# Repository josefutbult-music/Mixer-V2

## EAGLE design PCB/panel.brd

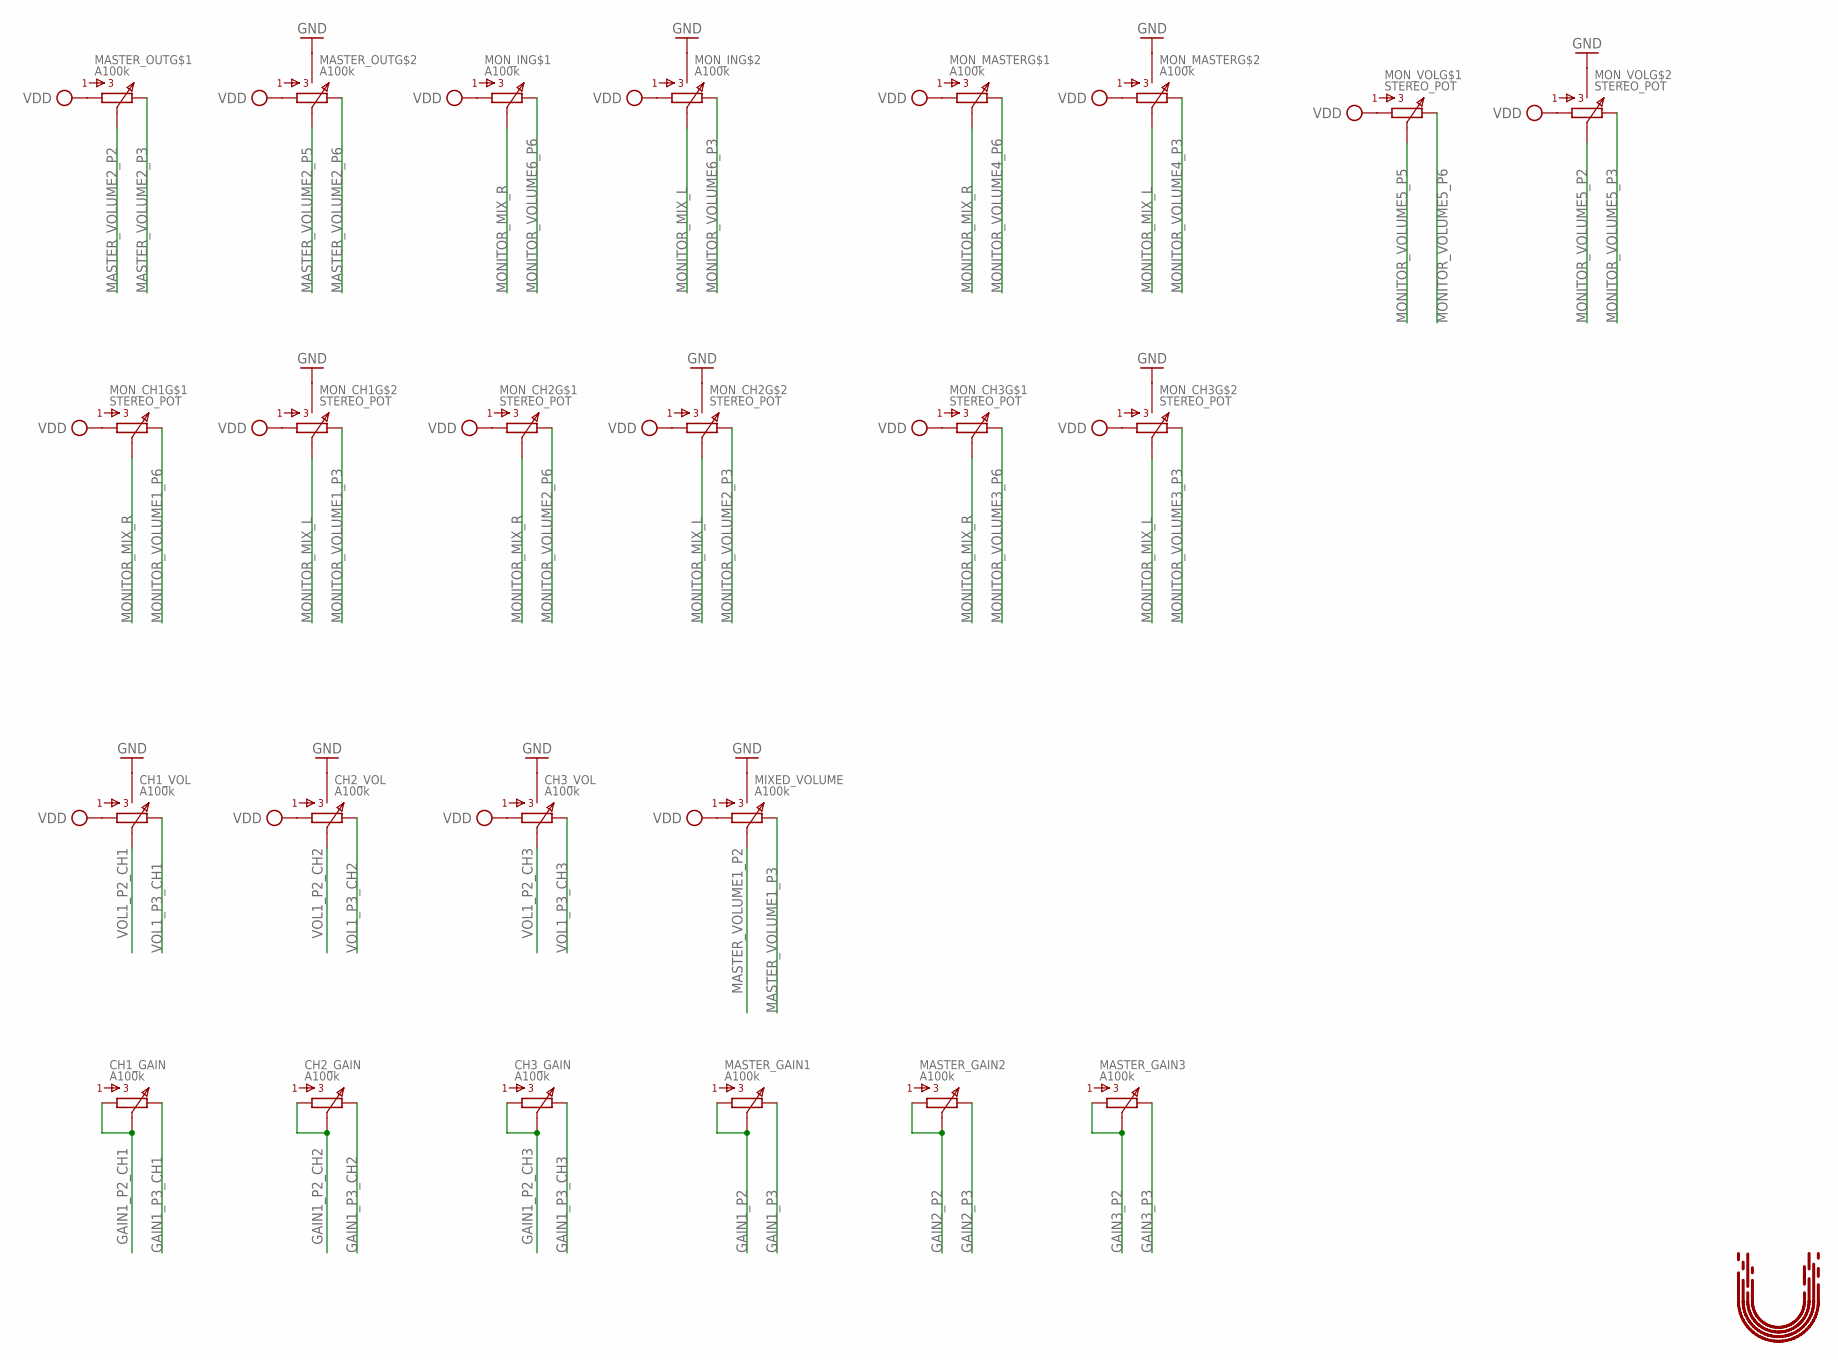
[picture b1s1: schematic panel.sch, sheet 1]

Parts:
CH1_GAIN, CH2_GAIN, CH3_GAIN: A100k; 3296W
CH1_VOL, CH2_VOL, CH3_VOL: A100k; P0915N
MASTER_GAIN1, MASTER_GAIN2, MASTER_GAIN3: A100k; 3296W
MASTER_OUT: A100k; P0925N
MIXED_VOLUME: A100k; P0915N
MON_CH1, MON_CH2, MON_CH3: STEREO_POT; P0925N
MON_IN: A100k; P0925N
MON_MASTER: A100k; P0925N
MON_VOL: STEREO_POT; P0925N
U$1: UTBULT_DESIGN4; UD_4

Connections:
GAIN1_P2: MASTER_GAIN1.P$1 (1), MASTER_GAIN1.P$2 (2); also elsewhere on the board
GAIN1_P2_CH1: CH1_GAIN.P$1 (1), CH1_GAIN.P$2 (2); also elsewhere on the board
GAIN1_P2_CH2: CH2_GAIN.P$1 (1), CH2_GAIN.P$2 (2); also elsewhere on the board
GAIN1_P2_CH3: CH3_GAIN.P$1 (1), CH3_GAIN.P$2 (2); also elsewhere on the board
GAIN1_P3: MASTER_GAIN1.P$3 (3); also elsewhere on the board
GAIN1_P3_CH1: CH1_GAIN.P$3 (3); also elsewhere on the board
GAIN1_P3_CH2: CH2_GAIN.P$3 (3); also elsewhere on the board
GAIN1_P3_CH3: CH3_GAIN.P$3 (3); also elsewhere on the board
GAIN2_P2: MASTER_GAIN2.P$1 (1), MASTER_GAIN2.P$2 (2); also elsewhere on the board
GAIN2_P3: MASTER_GAIN2.P$3 (3); also elsewhere on the board
GAIN3_P2: MASTER_GAIN3.P$1 (1), MASTER_GAIN3.P$2 (2); also elsewhere on the board
GAIN3_P3: MASTER_GAIN3.P$3 (3); also elsewhere on the board
GND: CH1_VOL.P$7, CH1_VOL.P$8, CH2_VOL.P$7, CH2_VOL.P$8, CH3_VOL.P$7, CH3_VOL.P$8, MASTER_OUT.P$7, MASTER_OUT.P$8, MIXED_VOLUME.P$7, MIXED_VOLUME.P$8, MON_CH1.P$7, MON_CH1.P$8, MON_CH2.P$7, MON_CH2.P$8, MON_CH3.P$7, MON_CH3.P$8, MON_IN.P$7, MON_IN.P$8, MON_MASTER.P$7, MON_MASTER.P$8, MON_VOL.P$7, MON_VOL.P$8; also elsewhere on the board
MASTER_VOLUME1_P2: MIXED_VOLUME.P$2 (2); also elsewhere on the board
MASTER_VOLUME1_P3: MIXED_VOLUME.P$3 (3); also elsewhere on the board
MASTER_VOLUME2_P2: MASTER_OUT.P$2 (2); also elsewhere on the board
MASTER_VOLUME2_P3: MASTER_OUT.P$3 (3); also elsewhere on the board
MASTER_VOLUME2_P5: MASTER_OUT.P$5 (2); also elsewhere on the board
MASTER_VOLUME2_P6: MASTER_OUT.P$6 (3); also elsewhere on the board
MONITOR_MIX_L: MON_CH1.P$5 (2), MON_CH2.P$5 (2), MON_CH3.P$5 (2), MON_IN.P$5 (2), MON_MASTER.P$5 (2); also elsewhere on the board
MONITOR_MIX_R: MON_CH1.P$2 (2), MON_CH2.P$2 (2), MON_CH3.P$2 (2), MON_IN.P$2 (2), MON_MASTER.P$2 (2); also elsewhere on the board
MONITOR_VOLUME1_P3: MON_CH1.P$6 (3); also elsewhere on the board
MONITOR_VOLUME1_P6: MON_CH1.P$3 (3); also elsewhere on the board
MONITOR_VOLUME2_P3: MON_CH2.P$6 (3); also elsewhere on the board
MONITOR_VOLUME2_P6: MON_CH2.P$3 (3); also elsewhere on the board
MONITOR_VOLUME3_P3: MON_CH3.P$6 (3); also elsewhere on the board
MONITOR_VOLUME3_P6: MON_CH3.P$3 (3); also elsewhere on the board
MONITOR_VOLUME4_P3: MON_MASTER.P$6 (3); also elsewhere on the board
MONITOR_VOLUME4_P6: MON_MASTER.P$3 (3); also elsewhere on the board
MONITOR_VOLUME5_P2: MON_VOL.P$5 (2); also elsewhere on the board
MONITOR_VOLUME5_P3: MON_VOL.P$6 (3); also elsewhere on the board
MONITOR_VOLUME5_P5: MON_VOL.P$2 (2); also elsewhere on the board
MONITOR_VOLUME5_P6: MON_VOL.P$3 (3); also elsewhere on the board
MONITOR_VOLUME6_P3: MON_IN.P$6 (3); also elsewhere on the board
MONITOR_VOLUME6_P6: MON_IN.P$3 (3); also elsewhere on the board
VDD: CH1_VOL.P$1 (1), CH2_VOL.P$1 (1), CH3_VOL.P$1 (1), MASTER_OUT.P$1 (1), MASTER_OUT.P$4 (1), MIXED_VOLUME.P$1 (1), MON_CH1.P$1 (1), MON_CH1.P$4 (1), MON_CH2.P$1 (1), MON_CH2.P$4 (1), MON_CH3.P$1 (1), MON_CH3.P$4 (1), MON_IN.P$1 (1), MON_IN.P$4 (1), MON_MASTER.P$1 (1), MON_MASTER.P$4 (1), MON_VOL.P$1 (1), MON_VOL.P$4 (1); also elsewhere on the board
VOL1_P2_CH1: CH1_VOL.P$2 (2); also elsewhere on the board
VOL1_P2_CH2: CH2_VOL.P$2 (2); also elsewhere on the board
VOL1_P2_CH3: CH3_VOL.P$2 (2); also elsewhere on the board
VOL1_P3_CH1: CH1_VOL.P$3 (3); also elsewhere on the board
VOL1_P3_CH2: CH2_VOL.P$3 (3); also elsewhere on the board
VOL1_P3_CH3: CH3_VOL.P$3 (3); also elsewhere on the board

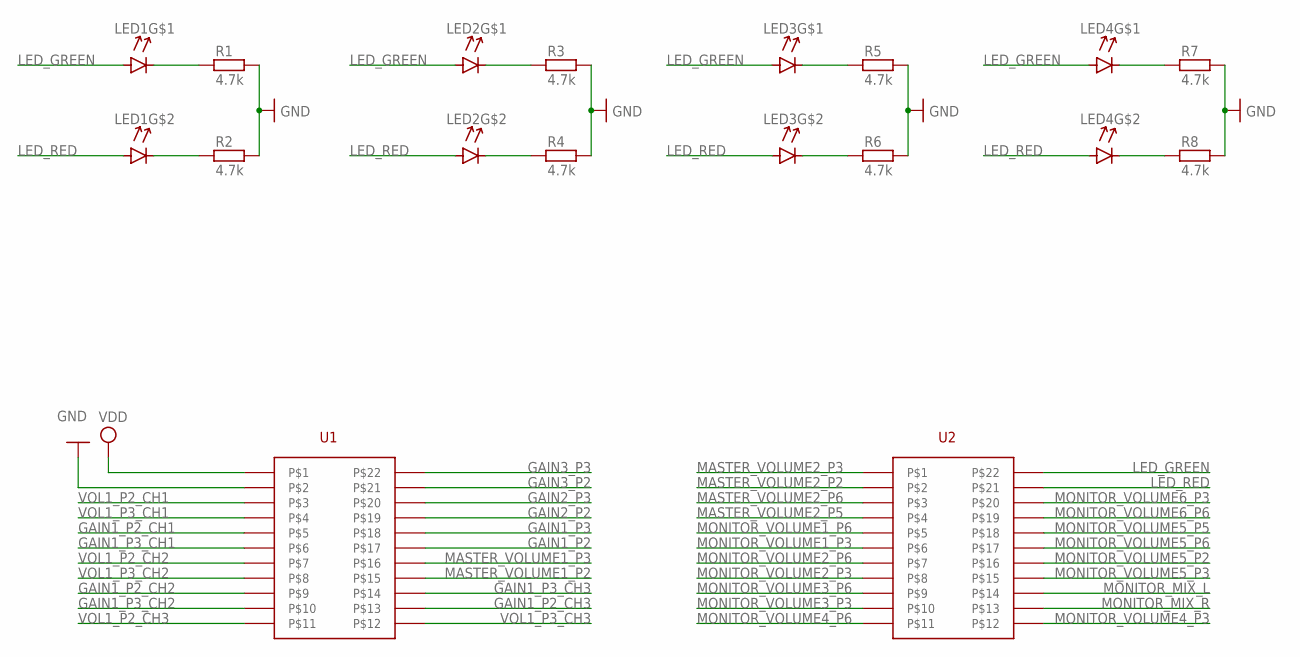
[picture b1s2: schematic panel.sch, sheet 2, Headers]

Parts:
LED1, LED2, LED3, LED4: DUAL_LEDDUAL_LED; RESCAXE40P80X160X50-4N
R1, R2, R3, R4, R5, R6, R7, R8: 4.7k; R0603
U1, U2: 22PINHEADER22PINHEADER; HDRV22W64P254_2X11_2794X508X838B

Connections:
GAIN1_P2: U1.17; also elsewhere on the board
GAIN1_P2_CH1: U1.5; also elsewhere on the board
GAIN1_P2_CH2: U1.9; also elsewhere on the board
GAIN1_P2_CH3: U1.13; also elsewhere on the board
GAIN1_P3: U1.18; also elsewhere on the board
GAIN1_P3_CH1: U1.6; also elsewhere on the board
GAIN1_P3_CH2: U1.10; also elsewhere on the board
GAIN1_P3_CH3: U1.14; also elsewhere on the board
GAIN2_P2: U1.19; also elsewhere on the board
GAIN2_P3: U1.20; also elsewhere on the board
GAIN3_P2: U1.21; also elsewhere on the board
GAIN3_P3: U1.22; also elsewhere on the board
GND: R1.2, R2.2, R3.2, R4.2, R5.2, R6.2, R7.2, R8.2, U1.2; also elsewhere on the board
LED_GREEN: LED1.1 (A), LED2.1 (A), LED3.1 (A), LED4.1 (A), U2.22
LED_RED: LED1.2 (A), LED2.2 (A), LED3.2 (A), LED4.2 (A), U2.21
MASTER_VOLUME1_P2: U1.15; also elsewhere on the board
MASTER_VOLUME1_P3: U1.16; also elsewhere on the board
MASTER_VOLUME2_P2: U2.2; also elsewhere on the board
MASTER_VOLUME2_P3: U2.1; also elsewhere on the board
MASTER_VOLUME2_P5: U2.4; also elsewhere on the board
MASTER_VOLUME2_P6: U2.3; also elsewhere on the board
MONITOR_MIX_L: U2.14; also elsewhere on the board
MONITOR_MIX_R: U2.13; also elsewhere on the board
MONITOR_VOLUME1_P3: U2.6; also elsewhere on the board
MONITOR_VOLUME1_P6: U2.5; also elsewhere on the board
MONITOR_VOLUME2_P3: U2.8; also elsewhere on the board
MONITOR_VOLUME2_P6: U2.7; also elsewhere on the board
MONITOR_VOLUME3_P3: U2.10; also elsewhere on the board
MONITOR_VOLUME3_P6: U2.9; also elsewhere on the board
MONITOR_VOLUME4_P3: U2.12; also elsewhere on the board
MONITOR_VOLUME4_P6: U2.11; also elsewhere on the board
MONITOR_VOLUME5_P2: U2.16; also elsewhere on the board
MONITOR_VOLUME5_P3: U2.15; also elsewhere on the board
MONITOR_VOLUME5_P5: U2.18; also elsewhere on the board
MONITOR_VOLUME5_P6: U2.17; also elsewhere on the board
MONITOR_VOLUME6_P3: U2.20; also elsewhere on the board
MONITOR_VOLUME6_P6: U2.19; also elsewhere on the board
unnamed: LED1.4 (C), R1.1
unnamed: LED1.3 (C), R2.1
unnamed: LED2.4 (C), R3.1
unnamed: LED2.3 (C), R4.1
unnamed: LED3.4 (C), R5.1
unnamed: LED3.3 (C), R6.1
unnamed: LED4.4 (C), R7.1
unnamed: LED4.3 (C), R8.1
VDD: U1.1; also elsewhere on the board
VOL1_P2_CH1: U1.3; also elsewhere on the board
VOL1_P2_CH2: U1.7; also elsewhere on the board
VOL1_P2_CH3: U1.11; also elsewhere on the board
VOL1_P3_CH1: U1.4; also elsewhere on the board
VOL1_P3_CH2: U1.8; also elsewhere on the board
VOL1_P3_CH3: U1.12; also elsewhere on the board

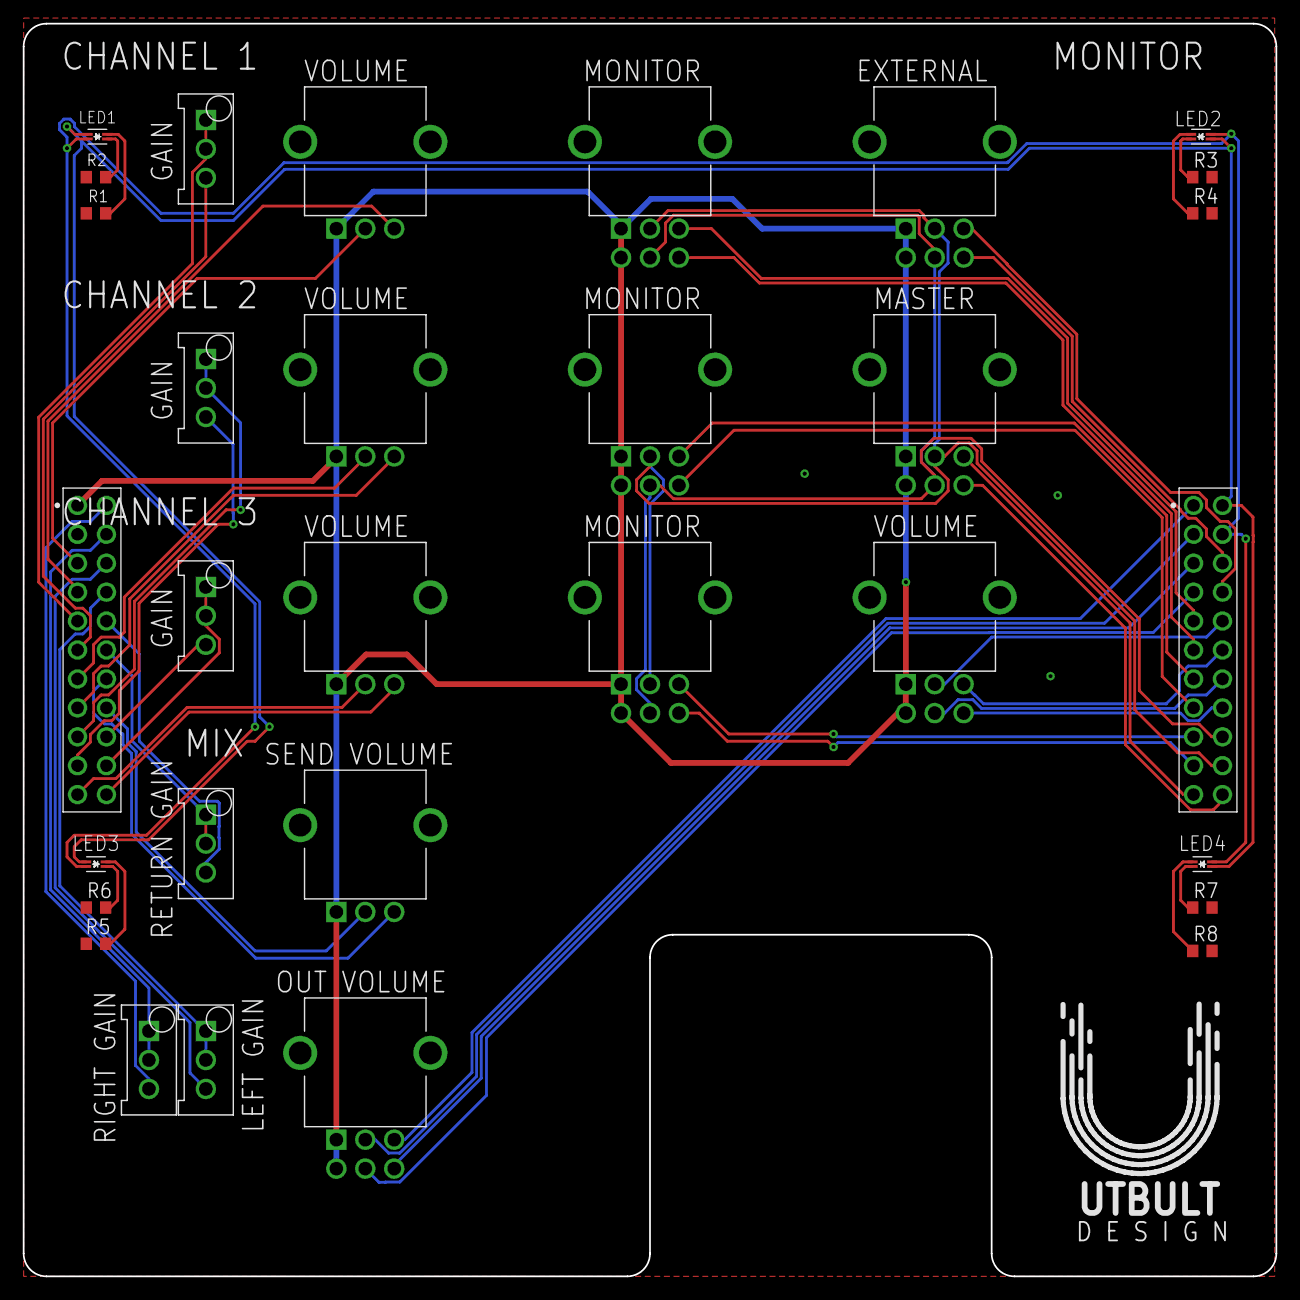
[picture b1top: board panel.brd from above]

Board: 2 copper layers, 110.0 x 110.0 mm, 32 parts (0 on the bottom side), 52 nets.

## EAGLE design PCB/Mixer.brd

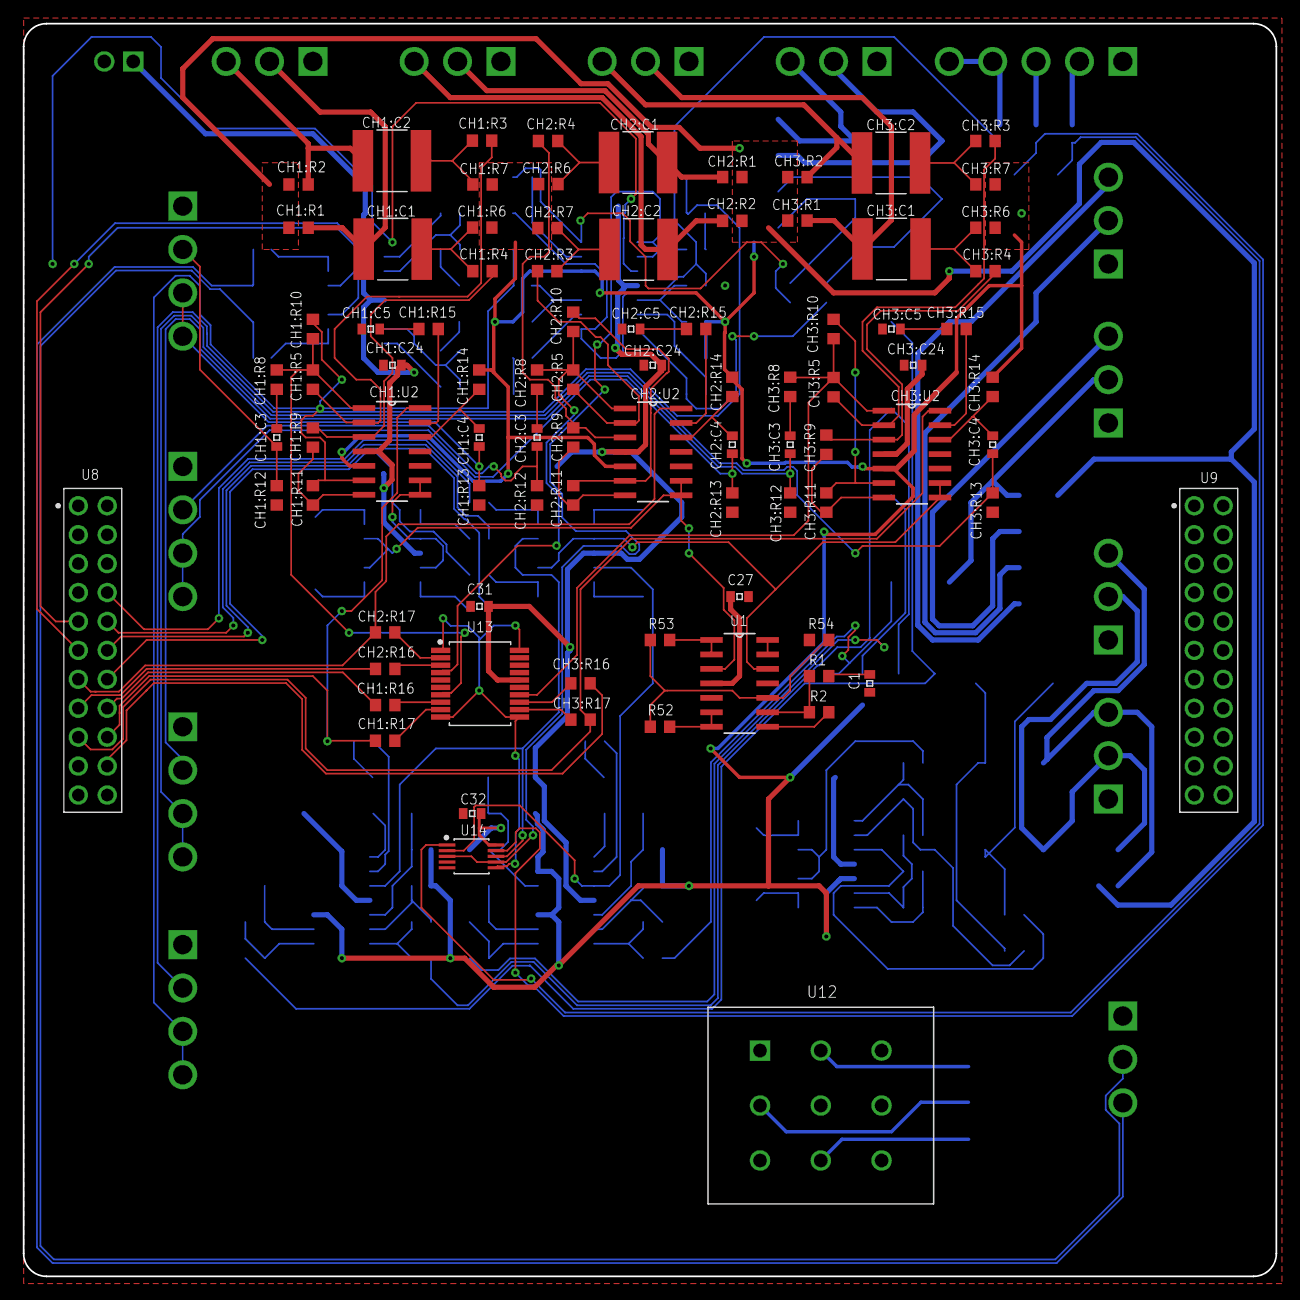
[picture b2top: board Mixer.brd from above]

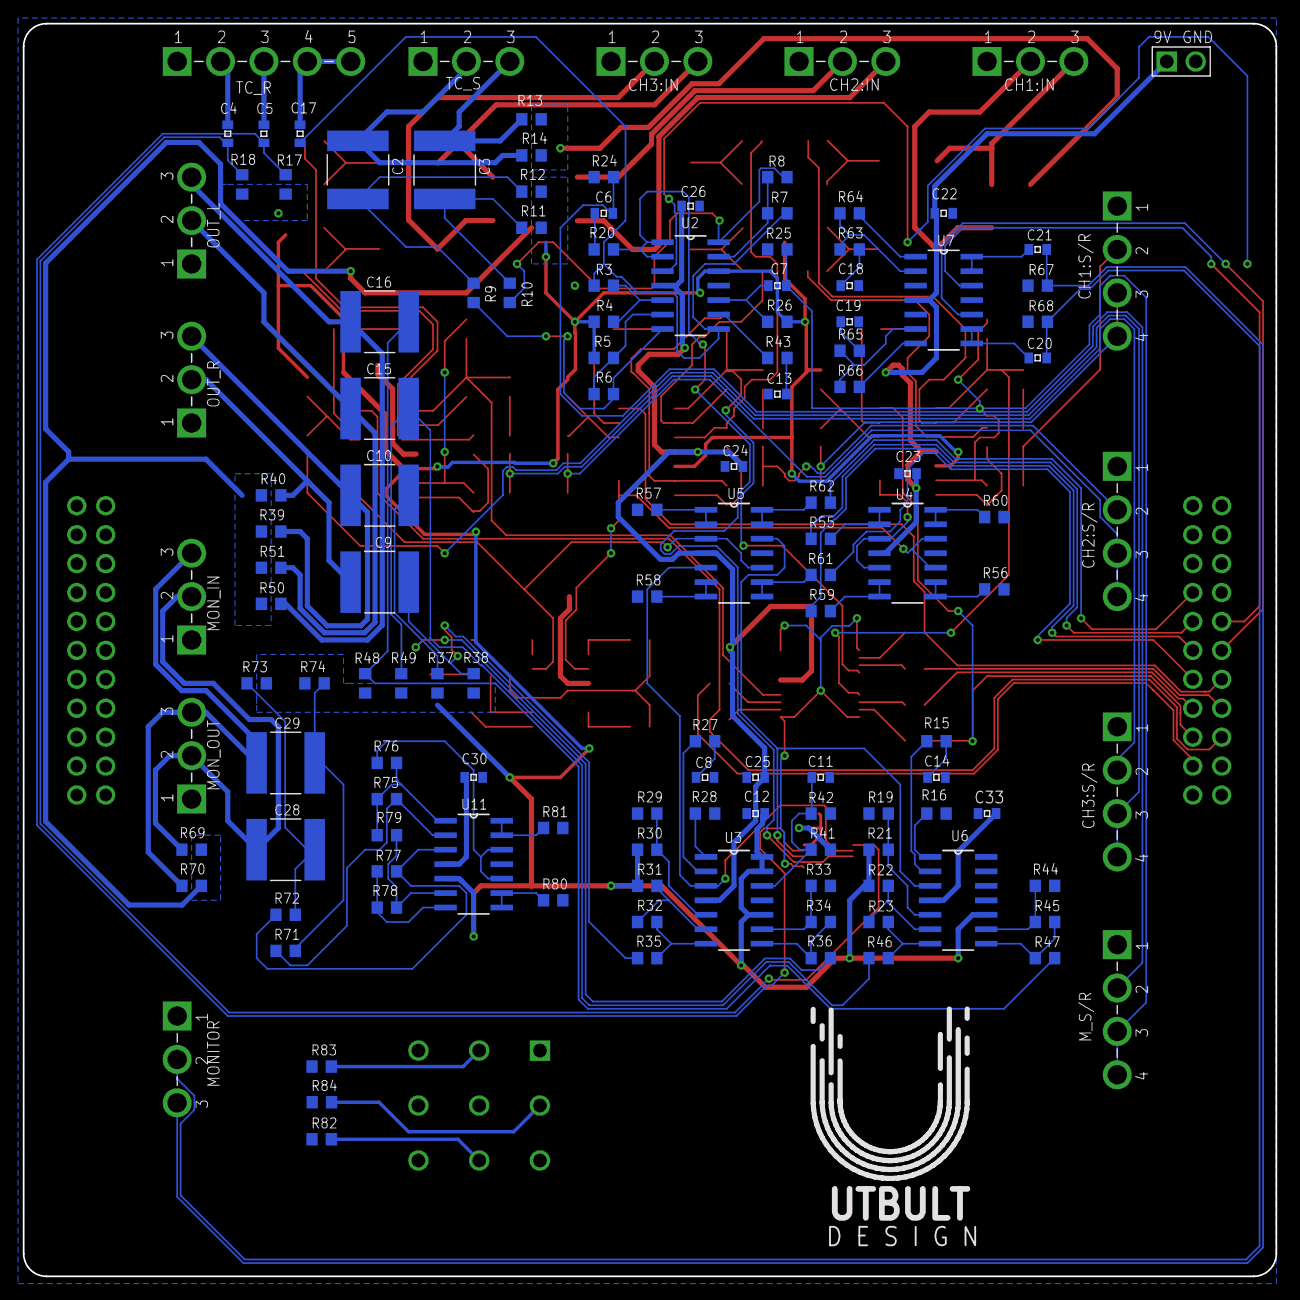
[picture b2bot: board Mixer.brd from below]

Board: 2 copper layers, 110.0 x 110.0 mm, 218 parts (131 on the bottom side), 176 nets.

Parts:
C1, C8, C13, C14, C18, C19: 4.7u; 0603
C2, C3, C9, C10, C15, C16, C28, C29: 22u / 63V; 2220
C4, C5, C6, C7, C17, C20, C21: 22u / 10V; 0603
C11, C12: 10u; 0603
C22, C23, C24, C25, C26, C27, C30, C33: 10u / 16V; 0603
C31, C32: 100n/16V; 0603
CH1:C1, CH1:C2, CH2:C1, CH2:C2, CH3:C1, CH3:C2: 22u / 63V; 2220
CH1:C3, CH1:C4, CH2:C3, CH2:C4, CH3:C3, CH3:C4: 22u / 10V; 0603
CH1:C5, CH2:C5, CH3:C5: 4.7u; 0603
CH1:C24, CH2:C24, CH3:C24: 10u / 16V; 0603
CH1:IN, CH2:IN, CH3:IN: XLR_Female; 3_PIN_PORT
CH1:R1, CH1:R2, CH1:R6, CH1:R7, CH1:R12, CH1:R13, CH1:R14, CH2:R1, CH2:R2, CH2:R6, CH2:R7, CH2:R12, CH2:R13, CH2:R14, CH3:R1, CH3:R2, CH3:R6, CH3:R7, CH3:R12, CH3:R13, CH3:R14: 100k; R0603
CH1:R3, CH1:R4, CH1:R5, CH1:R9, CH1:R10, CH1:R11, CH1:R15, CH1:R16, CH2:R3, CH2:R4, CH2:R5, CH2:R9, CH2:R10, CH2:R11, CH2:R15, CH2:R16, CH3:R3, CH3:R4, CH3:R5, CH3:R9, CH3:R10, CH3:R11, CH3:R15, CH3:R16: 10k; R0603
CH1:R8, CH1:R17, CH2:R8, CH2:R17, CH3:R8, CH3:R17: 100R; R0603
CH1:S/R, CH2:S/R, CH3:S/R: Switchable_jack; 4_PIN_PORT
CH1:U2, CH2:U2, CH3:U2: TL074IDT; SOIC127P600X175-14N
MONITOR: Stereojack; 3_PIN_PORT
MON_IN: XLR_Female; 3_PIN_PORT
MON_OUT: XLR_Male; 3_PIN_PORT
M_S/R: Switchable_jack; 4_PIN_PORT
OUT_L: XLR_Male; 3_PIN_PORT
OUT_R: XLR_Male; 3_PIN_PORT
R1, R3, R4, R5, R6, R7, R8, R15, R16, R19, R21, R22, R23, R27, R28, R29, R30, R31, R32, R33, R34, R43, R44, R45, R63, R65, R71, R72, R75, R77, R78, R79, R82, R83: 10k; R0603
R2, R64, R66: 5k; R0603
R9, R10, R20, R35, R36, R46, R47, R52, R53, R54, R55, R56, R57, R58, R59, R60, R61, R62, R76, R80, R81: 100R; R0603
R11, R12, R13, R14, R17, R18, R24, R25, R26, R37, R38, R39, R40, R41, R42, R48, R49, R50, R51, R67, R68, R69, R70, R73, R74: 100k; R0603
R84: 1k; R0603
TC_R: Stereojack; 5_PIN_PORT
TC_S: XLR_Male; 3_PIN_PORT
U1, U2, U3, U4, U5, U6, U7, U11: TL074IDT; SOIC127P600X175-14N
U8, U9: 22PINHEADER22PINHEADER; HDRV22W64P254_2X11_2794X508X838B
U10: POWER
U12: 3PDTSWITCH; FS57003PLT2B2M1QE
U13: ISL43240IAZ; SOP65P777X173-20N
U14: ISL43410IUZ; SOP50P490X110-10N
U$1: UTBULT_DESIGN4; UD_4

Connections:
+9V: C22.2, C23.2, C24.2, C25.2, C26.2, C27.2, C30.2, C31.1, C32.1, C33.2, CH1:C24.2, CH1:U2.4, CH2:C24.2, CH2:U2.4, CH3:C24.2, CH3:U2.4, R41.2, U1.4, U2.4, U3.4, U4.4, U5.4, U6.4, U7.4, U10.P$1, U11.4, U12.P$1, U12.P$5, U13.16, U14.10
CH1:N$1: CH1:C2.1, CH1:IN.P$3, CH1:R2.1
CH1:N$2: CH1:C1.1, CH1:IN.P$2, CH1:R1.1
CH1:N$3: CH1:R4.1, CH1:R9.2, CH1:U2.3
CH1:N$4: CH1:R3.2, CH1:R5.1, CH1:U2.2
CH1:N$5: CH1:C2.2, CH1:R3.1, CH1:R7.2
CH1:N$6: CH1:C1.2, CH1:R4.2, CH1:R6.2
CH1:N$7: CH1:R10.1, CH1:R11.2, CH1:U2.6
CH1:N$8: CH1:R9.1, CH1:R11.1, CH1:U2.7
CH1:N$10: CH1:C3.2, CH1:R12.2, CH1:S/R.P$2
CH1:N$11: CH1:C4.1, CH1:R13.2, CH1:S/R.P$3, CH1:S/R.P$4
CH1:N$12: CH1:C4.2, CH1:R14.2, CH1:U2.12
CH1:N$14: CH1:C5.1, CH1:R15.1
CH1:N$15: CH1:C3.1, CH1:R8.2
CH1_OUT: CH1:U2.8, CH1:U2.9, U1.5, U4.3, U4.5
CH2:N$1: CH2:C2.1, CH2:IN.P$3, CH2:R2.1
CH2:N$2: CH2:C1.1, CH2:IN.P$2, CH2:R1.1
CH2:N$3: CH2:R4.1, CH2:R9.2, CH2:U2.3
CH2:N$4: CH2:R3.2, CH2:R5.1, CH2:U2.2
CH2:N$5: CH2:C2.2, CH2:R3.1, CH2:R7.2
CH2:N$6: CH2:C1.2, CH2:R4.2, CH2:R6.2
CH2:N$7: CH2:R10.1, CH2:R11.2, CH2:U2.6
CH2:N$8: CH2:R9.1, CH2:R11.1, CH2:U2.7
CH2:N$10: CH2:C3.2, CH2:R12.2, CH2:S/R.P$2
CH2:N$11: CH2:C4.1, CH2:R13.2, CH2:S/R.P$3, CH2:S/R.P$4
CH2:N$12: CH2:C4.2, CH2:R14.2, CH2:U2.12
CH2:N$14: CH2:C5.1, CH2:R15.1
CH2:N$15: CH2:C3.1, CH2:R8.2
CH2_OUT: CH2:U2.8, CH2:U2.9, U1.3, U4.10, U4.12
CH3:N$1: CH3:C2.1, CH3:IN.P$3, CH3:R2.1
CH3:N$2: CH3:C1.1, CH3:IN.P$2, CH3:R1.1
CH3:N$3: CH3:R4.1, CH3:R9.2, CH3:U2.3
CH3:N$4: CH3:R3.2, CH3:R5.1, CH3:U2.2
CH3:N$5: CH3:C2.2, CH3:R3.1, CH3:R7.2
CH3:N$6: CH3:C1.2, CH3:R4.2, CH3:R6.2
CH3:N$7: CH3:R10.1, CH3:R11.2, CH3:U2.6
CH3:N$8: CH3:R9.1, CH3:R11.1, CH3:U2.7
CH3:N$10: CH3:C3.2, CH3:R12.2, CH3:S/R.P$2
CH3:N$11: CH3:C4.1, CH3:R13.2, CH3:S/R.P$3, CH3:S/R.P$4
CH3:N$12: CH3:C4.2, CH3:R14.2, CH3:U2.12
CH3:N$14: CH3:C5.1, CH3:R15.1
CH3:N$15: CH3:C3.1, CH3:R8.2
CH3_OUT: CH3:U2.8, CH3:U2.9, U1.12, U5.3, U5.10
GAIN1_P2: R43.2, U2.9, U9.6
GAIN1_P2_CH1: CH1:R15.2, CH1:U2.13, U9.18
GAIN1_P2_CH2: CH2:R15.2, CH2:U2.13, U9.16
GAIN1_P2_CH3: CH3:R15.2, CH3:U2.13, U8.12
GAIN1_P3_CH1: CH1:R17.1, CH1:U2.14, U8.14
GAIN1_P3_CH2: CH2:R17.1, CH2:U2.14, U8.7
GAIN1_P3_CH3: CH3:R17.1, CH3:U2.14, U8.9
GAIN2_P2: R27.2, U3.2, U9.5
GAIN2_P3: R28.1, U3.1, U8.20
GAIN3_P2: R15.2, U6.2, U8.21
GAIN3_P3: R16.1, U6.1, U8.22
GND: C1.2, C8.2, C11.2, C12.2, C13.2, C14.2, C18.2, C19.2, C22.1, C23.1, C24.1, C25.1, C26.1, C27.1, C30.1, C31.2, C32.2, C33.1, CH1:C5.2, CH1:C24.1, CH1:IN.P$1, CH1:R12.1, CH1:R13.1, CH1:S/R.P$1, CH1:U2.11, CH2:C5.2, CH2:C24.1, CH2:IN.P$1, CH2:R12.1, CH2:R13.1, CH2:S/R.P$1, CH2:U2.11, CH3:C5.2, CH3:C24.1, CH3:IN.P$1, CH3:R12.1, CH3:R13.1, CH3:S/R.P$1, CH3:U2.11, MONITOR.P$1, MON_IN.P$1, MON_OUT.P$1, M_S/R.P$1, OUT_L.P$1, OUT_R.P$1, R24.1, R25.1, R42.1, R67.1, R68.1, R82.1, R83.1, TC_R.P$1, TC_S.P$1, U1.11, U2.11, U3.11, U4.11, U5.11, U6.11, U7.11, U8.2, U10.P$2, U11.11, U12.P$3, U12.P$7, U12.P$8, U12.P$9, U13.5, U13.6, U14.4, U14.5
LED_GREEN: R83.2, U9.22, U12.P$4
LED_RED: R82.2, U9.21, U12.P$6
MASTER_BYP: R20.1, U2.1, U2.2, U14.3, U14.7
MASTER_OUT_L: U5.12, U6.3, U14.8
MASTER_OUT_R: U3.3, U5.5, U14.2
MASTER_RETURN_L: C5.2, R17.2, U14.9
MASTER_RETURN_R: C4.2, R18.2, U14.1
MASTER_VOLUME1_P2: U2.3, U8.4
MASTER_VOLUME1_P3: R2.2, U1.8, U9.10
MASTER_VOLUME2_P2: R29.1, R33.1, U9.2
MASTER_VOLUME2_P3: R28.2, U9.1
MASTER_VOLUME2_P5: R19.1, R44.1, U9.4
MASTER_VOLUME2_P6: R16.2, U9.3
MONITOR_MIX_L: U7.5, U9.14
MONITOR_MIX_R: U7.3, U9.13
MONITOR_VOLUME1_P3: R59.2, U8.17
MONITOR_VOLUME1_P6: R55.2, U8.18
MONITOR_VOLUME2_P3: R60.2, U9.8
MONITOR_VOLUME2_P6: R56.2, U9.7
MONITOR_VOLUME3_P3: R61.2, U8.16
MONITOR_VOLUME3_P6: R57.2, U9.9
MONITOR_VOLUME4_P3: R62.2, U8.19
MONITOR_VOLUME4_P6: R58.2, U9.11
MONITOR_VOLUME5_P2: U7.10, U8.6
MONITOR_VOLUME5_P3: R66.2, U7.7, U9.15
MONITOR_VOLUME5_P5: U7.12, U8.5
MONITOR_VOLUME5_P6: R64.2, U7.1, U9.17
MONITOR_VOLUME6_P3: R81.2, U9.20
MONITOR_VOLUME6_P6: R80.2, U9.19
MON_IN: R76.2, U11.10, U11.12
unnamed: R52.2, R53.2, R54.2, U1.10
unnamed: R1.2, R2.1, U1.9
unnamed: C14.1, R15.1
unnamed: C1.1, R1.1
unnamed: R3.2, R4.2, U2.5
unnamed: R5.2, R6.1, U2.6
unnamed: R6.2, R9.1, U2.7
unnamed: R7.2, R8.1, U2.13
unnamed: R8.2, R10.1, U2.14
unnamed: C3.1, R10.2, R11.2
unnamed: C2.1, R9.2, R12.2
unnamed: R19.2, R21.2, U6.5
unnamed: C4.1, TC_R.P$2
unnamed: C5.1, TC_R.P$3
unnamed: R84.1, U12.P$2
unnamed: R22.2, R23.1, U6.6
unnamed: R23.2, R46.1, U6.7
unnamed: R44.2, R45.1, U6.9
unnamed: R45.2, R47.1, U6.8
unnamed: C7.1, M_S/R.P$3, M_S/R.P$4, R25.2
unnamed: C6.1, R20.2
unnamed: R29.2, R30.2, U3.5
unnamed: R31.2, R32.1, U3.6
unnamed: C8.1, R27.1
unnamed: C11.1, R41.1, R42.2, U3.12
unnamed: R32.2, R35.1, U3.7
unnamed: R33.2, R34.1, U3.9
unnamed: R34.2, R36.1, U3.8
unnamed: C10.1, R36.2, R37.2
unnamed: C9.1, R35.2, R38.2
unnamed: C10.2, OUT_R.P$3, R39.2
unnamed: C9.2, OUT_R.P$2, R40.2
unnamed: R52.1, U1.6, U1.7
unnamed: R55.1, U4.1, U4.2
unnamed: R56.1, U4.8, U4.9
unnamed: R53.1, U1.1, U1.2
unnamed: R59.1, U4.6, U4.7
unnamed: R60.1, U4.13, U4.14
unnamed: R54.1, U1.13, U1.14
unnamed: R57.1, U5.1, U5.2
unnamed: R61.1, U5.8, U5.9
unnamed: R63.2, R64.1, U7.2
unnamed: R58.1, U5.6, U5.7
unnamed: R62.1, U5.13, U5.14
unnamed: C18.1, R63.1
unnamed: R65.2, R66.1, U7.6
unnamed: C7.2, R26.2, U2.10
unnamed: C13.1, R43.1
unnamed: C16.1, R47.2, R48.2
unnamed: C15.1, R46.2, R49.2
unnamed: C16.2, OUT_L.P$3, R50.2
unnamed: C15.2, OUT_L.P$2, R51.2
unnamed: C17.1, TC_R.P$4, TC_R.P$5
unnamed: C19.1, R65.1
unnamed: C20.1, U7.8, U7.9
unnamed: C21.1, U7.13, U7.14
unnamed: C20.2, MONITOR.P$2, R68.2
unnamed: C21.2, MONITOR.P$3, R67.2
unnamed: C29.1, MON_IN.P$3, MON_OUT.P$3, R70.1
unnamed: C28.1, MON_IN.P$2, MON_OUT.P$2, R69.1
unnamed: C29.2, R71.1, R74.2
unnamed: C28.2, R72.2, R73.2
unnamed: R72.1, R77.2, U11.3
unnamed: R71.2, R75.1, U11.2
unnamed: R78.2, R79.1, U11.6
unnamed: R77.1, R78.1, U11.7
unnamed: R75.2, R76.1, R79.2, U11.1
unnamed: R80.1, U11.8, U11.9
unnamed: R81.1, U11.13, U11.14
PRE_TC: C17.2, R3.1, R7.1, U2.8, U9.12
SELECTOR: R84.2, U13.1, U13.10, U13.11, U13.20, U14.6
SR_BYP_CH1: CH1:R5.2, CH1:R8.1, CH1:R10.2, CH1:U2.1, U13.7
SR_BYP_CH2: CH2:R5.2, CH2:R8.1, CH2:R10.2, CH2:U2.1, U13.4
SR_BYP_CH3: CH3:R5.2, CH3:R8.1, CH3:R10.2, CH3:U2.1, U13.14
SR_OUT_CH1: CH1:R17.2, U13.9
SR_OUT_CH2: CH2:R17.2, U13.2
SR_OUT_CH3: CH3:R17.2, U13.12
SR_SEL_CH1: CH1:R16.1, U13.8
SR_SEL_CH2: CH2:R16.1, U13.3
SR_SEL_CH3: CH3:R16.1, U13.13
TC_OUT+: C2.2, R14.2, TC_S.P$2
TC_OUT-: C3.2, R13.2, TC_S.P$3
VDD: C12.1, CH1:R6.1, CH1:R7.1, CH1:R14.1, CH1:U2.5, CH2:R6.1, CH2:R7.1, CH2:R14.1, CH2:U2.5, CH3:R6.1, CH3:R7.1, CH3:R14.1, CH3:U2.5, R4.1, R5.1, R11.1, R12.1, R17.1, R18.1, R21.1, R22.1, R26.1, R30.1, R31.1, R37.1, R38.1, R48.1, R49.1, R73.1, R74.1, U2.12, U3.10, U3.13, U3.14, U6.10, U8.1, U11.5
VEE: CH1:R1.2, CH1:R2.2, CH2:R1.2, CH2:R2.2, CH3:R1.2, CH3:R2.2, R13.1, R14.1, R39.1, R40.1, R50.1, R51.1, R69.2, R70.2
VOL1_P2_CH1: CH1:U2.10, U8.3
VOL1_P2_CH2: CH2:U2.10, U8.10
VOL1_P2_CH3: CH3:U2.10, U8.11
VOL1_P3: C6.2, M_S/R.P$2, R24.2
VOL1_P3_CH1: CH1:R16.2, U8.15
VOL1_P3_CH2: CH2:R16.2, U8.8
VOL1_P3_CH3: CH3:R16.2, U8.13

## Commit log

2021-05-23 Init
2021-05-23 Add switch and analog selectors
2021-06-02 Semi done
2021-06-02 Fixed wiring on main board
2021-06-06 Updating to 2 layer
